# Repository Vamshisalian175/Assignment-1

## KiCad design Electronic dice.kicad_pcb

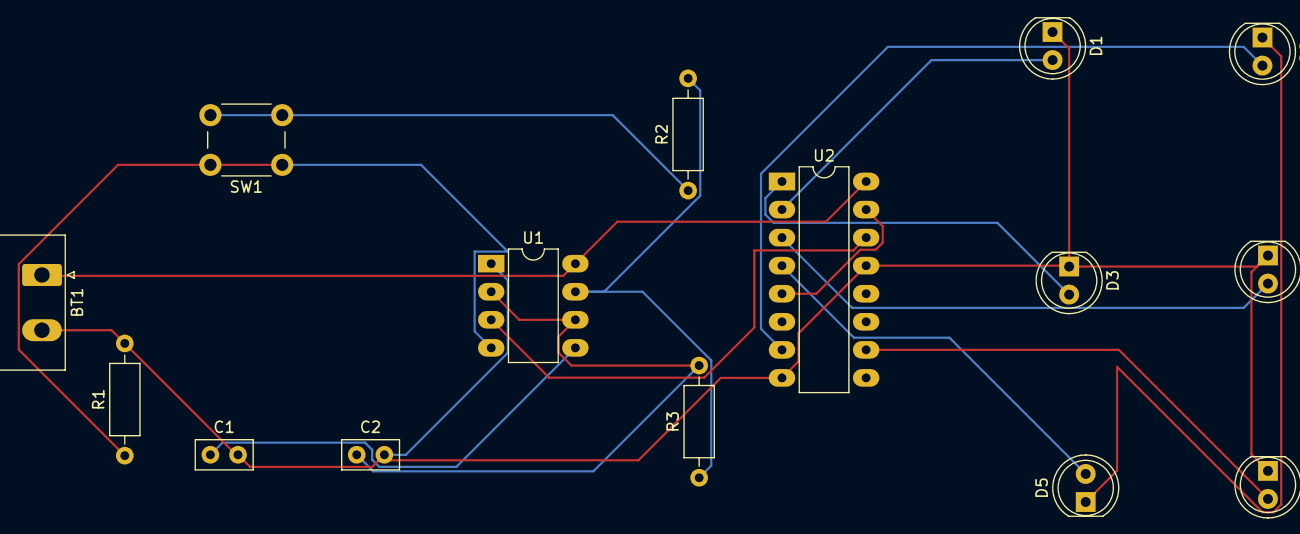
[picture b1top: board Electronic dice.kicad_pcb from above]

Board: 2 copper layers, 15 parts (0 on the bottom side), 16 nets.

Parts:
BT1: 9; PhoenixContact_MSTBA_2,5_2-G_1x02_P5.00mm_Horizontal
C1: 1nF; C_Disc_D5.0mm_W2.5mm_P2.50mm
C2: 0.1uF; C_Disc_D5.0mm_W2.5mm_P2.50mm
D1, D2, D3, D4, D5, D6: LED; LED_D5.0mm
R1: 2.2k; R_Axial_DIN0207_L6.3mm_D2.5mm_P10.16mm_Horizontal
R2, R3: 100K; R_Axial_DIN0207_L6.3mm_D2.5mm_P10.16mm_Horizontal
SW1: SW_Push; SW_PUSH_6mm
U1: NE555D; DIP-8_W7.62mm_LongPads
U2: 4017; DIP-16_W7.62mm_LongPads

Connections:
Earth: BT1.2 (-), C1.2, C2.2, D1.1 (K), D3.1 (K), D4.1 (K), D6.1 (K), R1.2, U1.1 (GND), U2.8 (VSS), U2.13 (CKEN)
unnamed: BT1.1 (+), U1.8 (VCC), U2.16 (VDD)
unnamed: D1.2 (A), U2.2 (Q1)
unnamed: D2.2 (A), U2.7 (Q3)
unnamed: D2.1 (K), D5.1 (K)
unnamed: D3.2 (A), U2.1 (Q5)
unnamed: D4.2 (A), U2.3 (Q0)
unnamed: D5.2 (A), U2.4 (Q2)
unnamed: D6.2 (A), U2.10 (Q4)
unnamed: R2.1, SW1.2
unnamed: C1.1, U1.5 (CV)
unnamed: R2.2, R3.1, U1.7 (DIS)
unnamed: U1.3 (Q), U2.14 (CLK)
unnamed: R1.1, SW1.1, U1.4 (R)
unnamed: C2.1, R3.2, U1.2 (TR), U1.6 (THR)
unnamed: U2.5 (Q6), U2.15 (Reset)
